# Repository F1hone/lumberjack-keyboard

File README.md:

# Lumberjack - Through-hole ortholinear 60% keyboard PCB

Lumberjack is a split 5x12 ortholinear keyboard PCB using through-hole components only.

The goal of this project is to build an all through-hole component ortholinear PCB that fits in a standard 60% tray mount case.

Inspired by the [Plaid keyboard](https://github.com/hsgw/plaid).

* Designed to be easy to build with minimal soldering experience.
* All through-hole components, no SMD soldering required.
* Get that visible component aesthetic in a standard 60% tray-mount case.
* Supports both USB Mini and USB-C.
* Plateless or with FR4 switch plates.

# Ordering parts

See the [Bill of materials](BOM.md) for a detailed list of the required parts.

PCBs can be manufactuered by a variety of online PCB fabricators. You can use [PCBShopper](https://pcbshopper.com/) to search for the best price.

The [zip file in the gerber directory](https://github.com/peej/lumberjack-keyboard/blob/master/gerber/lumberjack.zip) contains the gerber files your fabricator will need to make the PCB.

When uploading the gerber zip files, use the default PCB settings.

Note that when uploading to JLCPCB, the upload tool may not detect the dimensions of the PCB from the gerber files and may not generate a preview image. This appears to be an issue with JLCPCB and you can manually enter the PCB size as 94.6x285mm.

If you want to use a plate, there are gerbers for an FR4 plate. You will need two plates, one for each half of the keyboard.

# Construction

Solder all the components onto the top side of the PCB except the USB connector which should be on the back of the board. Leave the larger components until last so that the board will lie flat upsidedown while you solder the resistors and capacitors.

Take care to put the correct value resistors and capacitors in the correct places, the values are written on the silkmask along with the component reference. If you are unsure about the value of a resistor, check it with a multimeter.

Ensure that polarised components (diodes, LEDs, electrolytic capacitor (C3), IC socket) are in the correct orientation. The square pad is for the negative side of the component; for a diode this means the side with the black stripe; for LEDs and C3 the short leg is the cathode and goes in the square pad.

See [the build guide](guide.md) for more information.

## Need help?

Have questions or need help, reach out via [our Discord server](https://discord.gg/cQ9EXqQmpE) where you will find many helpful Lumberjack owners.

# Firmware

Firmware is available in the QMK repository under the name `peej/lumberjack`.

Follow the [QMK firmware instructions](https://docs.qmk.fm/#/flashing) to build and flash the firmware.

To put the board into bootloader mode so it is ready to recieve firmware, press and hold the BOOT button (SW2) while pressing and releasing the RESET button (SW1). The board will now be detected as an USBasp device and can have the firmware flashed via the USB port.

Pressing the RESET button (SW1) on its own will restart the microprocessor. Once flashed with firmware it is neccessary to reset the keyboard so as to return control to the new firmware.

Note that due to the BOOT button (SW2) sharing a pin with column 3, when pressed the keys in that column will also activate. This is expected behavour but can be a little annoying or confusing if you are not expecting it.

## VIA

There is a VIA compatible firmware available in QMK. With this firmware flashed, the board will be automatically recognised by VIA when you plug it in.

## Bootloader

If you have a "raw" chip without a bootloader, you will need to compile and flash the bootloader onto the chip via another device. [See the build guide for more information](guide.md#bootloader).

## Matrix information

If you are building your own firmware, the following matrix information will be useful to you:

| Configuration   | Value                                  |
|-----------------|----------------------------------------|
| MATRIX_ROWS     | 6                                      |
| MATRIX_COLS     | 10                                     |
| MATRIX_ROW_PINS | C0, B5, B4, B3, B2, B1                 |
| MATRIX_COL_PINS | B0, D7, D6, D5, D4, D1, D0, C1, C2, C3 |
| DIODE_DIRECTION | COL2ROW                                |

Due to the limited pin number of the ATMEGA328P, the PCB uses a 6 by 10 matrix (16 pins) instead of a 5 by 12 matrix (17 pins), this makes organising the matrix in your firmware slightly more complicated. The image below shows pins for each key.

# Component cover

Cut a piece of 2mm thick acrylic to size (95x57mm) and drill 4 m2 holes in the corners for the standoffs. Use the PCB or cover.dxf as a guide for the hole positions, you can also use cover.dxf for laser cutting the correct size acrylic.

Affix the 4 standoffs to the PCB with screws from underneath the PCB. Use the remaining 4 screws to attach the acrylic to the top of the standoffs.

# Electronic component cradles

Want to give your components the comfort they need, right?

These 3d printable cradles for your electornic components provided by 
SuPaSeM#3659 (discord) will hold things in place, keep them neat and tidy, and cradle your components like a baby.

# Revisions

## Rev 1.1

* Fix cosmetic errors in silkscreen
* Increase resistor footprint size
* Fix R1 resistor connection to D-

## Rev 1.2

* Add JST socket footprint for USB daughterboard
* Rotate central mount hole 90 degrees

## Rev 1.3

* Add hybrid USB port footprint for mini and type C
* Fix numbering of zener diode footprints
* Flip MX7 to be south facing

## Rev 1.4

* Use USB footprint with better positioning
* Move 5.1k resistors to better location
* Change MX8 to allow both north and south facing switch
## Rev 1.5

* Change board outline to include cutouts for Bakeneko 60
* Re-route traces away from edges of the board
* Change MX footprints to MX/Alps/Choc combined footprint
* Add through-hole JST connector footprint
* Add silkscreen art to underside

## Rev 1.6

* Add mounting holes for standoffs so PCB can be used without a case

## Rev 1.7

* Change board outline to include cutouts for Cannon Keys Bakeneko and Singa Unikorn

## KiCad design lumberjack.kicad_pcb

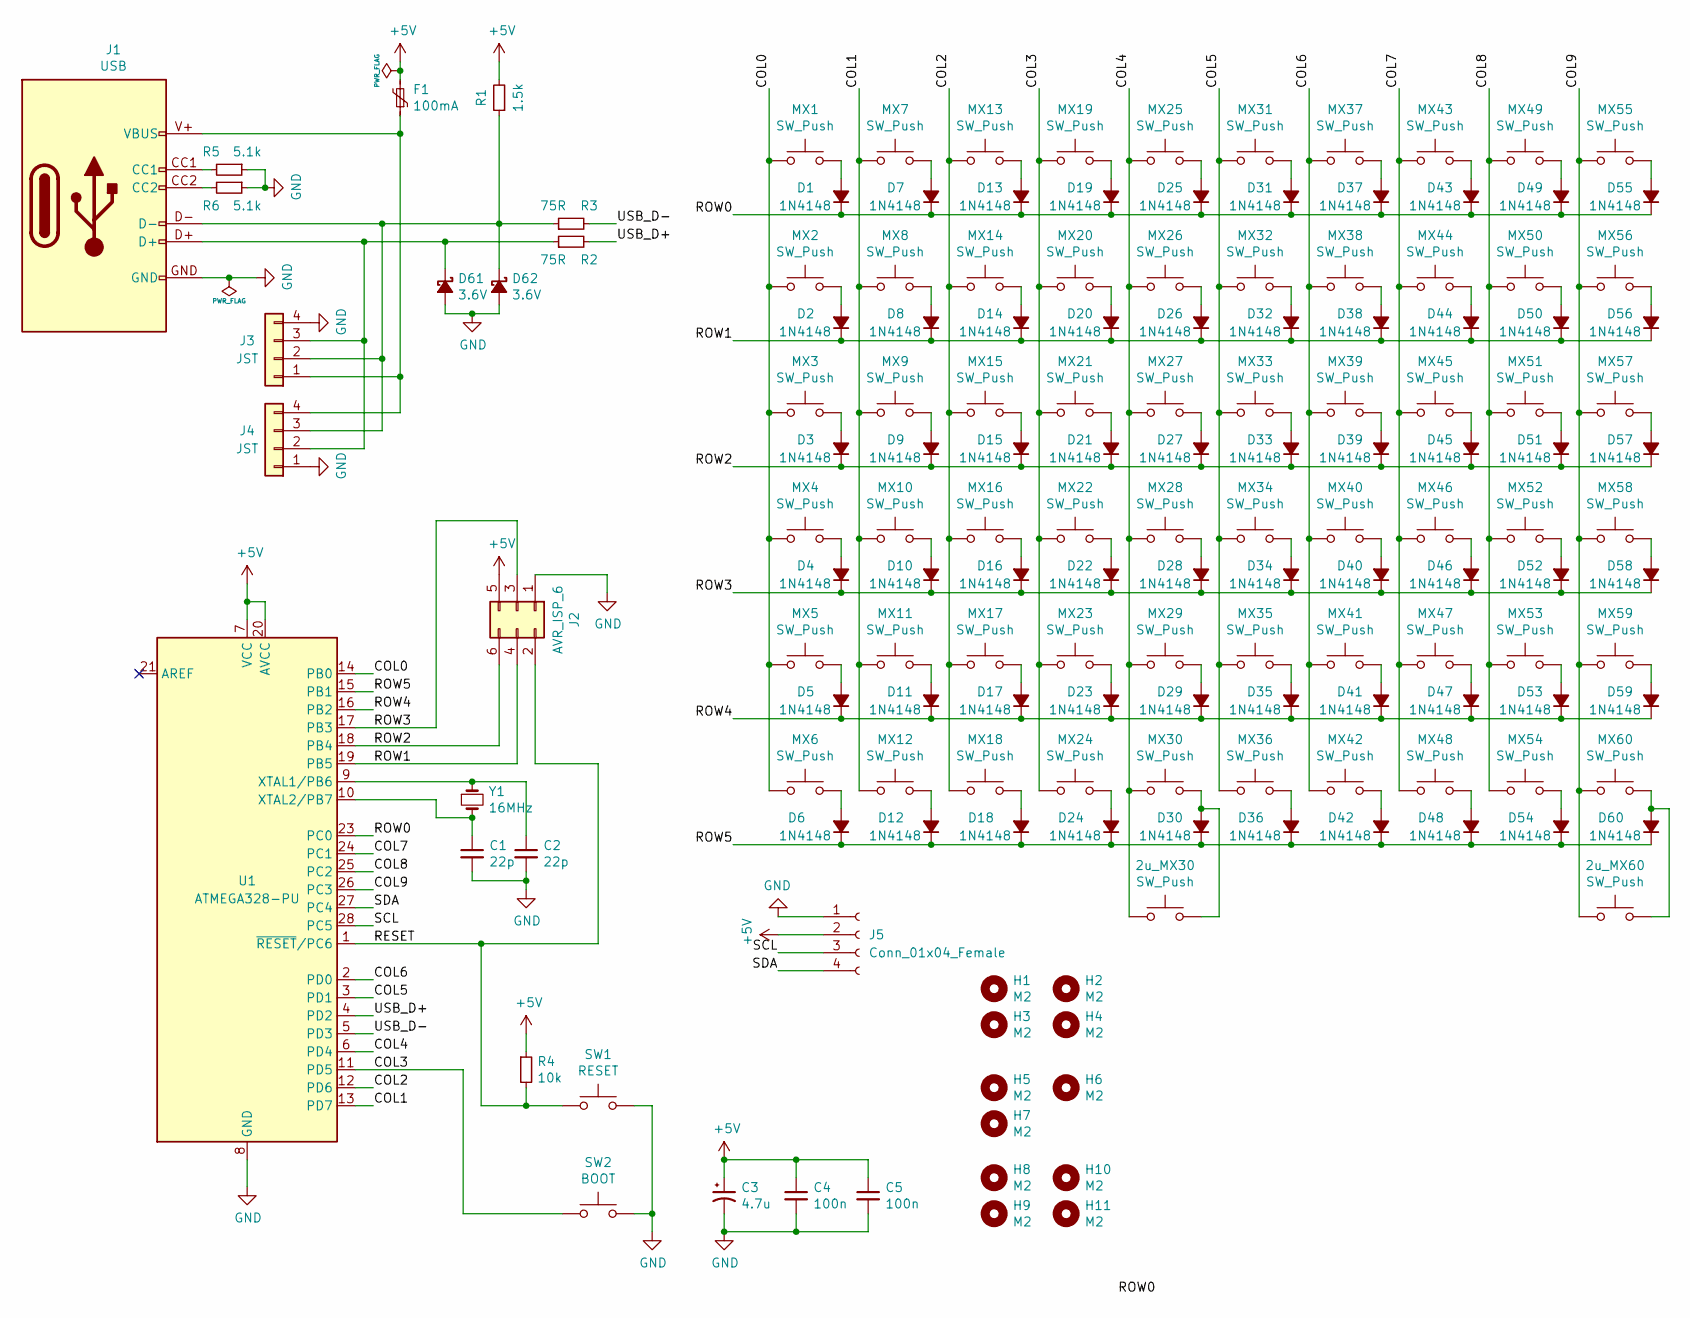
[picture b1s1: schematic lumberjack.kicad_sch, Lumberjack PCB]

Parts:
2u_MX30, 2u_MX60: SW_Push; MX_PCB_200B
C1, C2: 22p; C_Disc_D3.0mm_W1.6mm_P2.50mm
C3: 4.7u; CP_Radial_D4.0mm_P1.50mm
C4, C5: 100n; C_Disc_D4.3mm_W1.9mm_P5.00mm
D1, D2, D3, D4, D5, D6, D7, D8, D9, D10, D11, D12, D13, D14, D15, D16, D17, D18, D19, D20, D21, D22, D23, D24, D25, D26, D27, D28, D29, D30, D31, D32, D33, D34, D35, D36, D37, D38, D39, D40, D41, D42, D43, D44, D45, D46, D47, D48, D49, D50, D51, D52, D53, D54, D55, D56, D57, D58, D59, D60: 1N4148; D_DO-35_SOD27_P7.62mm_Horizontal
D61, D62: 3.6V; D_DO-35_SOD27_P7.62mm_Horizontal
F1: 100mA; Fuse_Bourns_MF-RHT100
H1, H2, H3, H4, H8, H9, H10, H11: M2; MountingHole_M2
H5, H6, H7: M2; MountingSlot_M2
J1: USB; USB_Hybrid
J2: AVR_ISP_6; PinHeader_2x03_P2.54mm_Vertical
J3: JST; JST_SH_SM04B-SRSS-TB_1x04-1MP_P1.00mm_Horizontal
J4: JST; S4B-ZRLFSN
J5: Conn_01x04_Female; PinHeader_1x04_P2.54mm_Vertical
MX1, MX2, MX3, MX4, MX5, MX6, MX7, MX9, MX10, MX11, MX12, MX13, MX14, MX15, MX16, MX17, MX18, MX19, MX20, MX21, MX22, MX23, MX24, MX25, MX26, MX27, MX28, MX29, MX30, MX31, MX32, MX33, MX34, MX35, MX36, MX37, MX38, MX39, MX40, MX41, MX42, MX43, MX44, MX45, MX46, MX47, MX48, MX49, MX50, MX51, MX52, MX53, MX54, MX55, MX56, MX57, MX58, MX59, MX60: SW_Push; MX_Alps_Choc
MX8: SW_Push; MX_Alps_Choc_NTHSTH
R1: 1.5k; R_Axial_DIN0204_L3.6mm_D1.6mm_P7.62mm_Horizontal
R2, R3: 75R; R_Axial_DIN0204_L3.6mm_D1.6mm_P7.62mm_Horizontal
R4: 10k; R_Axial_DIN0204_L3.6mm_D1.6mm_P7.62mm_Horizontal
R5, R6: 5.1k; R_Axial_DIN0204_L3.6mm_D1.6mm_P7.62mm_Horizontal
SW1: RESET; SW_PUSH_6mm
SW2: BOOT; SW_PUSH_6mm
U1: ATMEGA328-PU; DIP-28_W7.62mm
Y1: 16MHz; Crystal_HC49-4H_Vertical

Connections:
+5V: C3.1, C4.1, C5.1, F1.2, J2.5, J5.2, R1.2, R4.1, U1.7 (VCC), U1.20 (AVCC)
/COL0: MX1.2, MX2.2, MX3.2, MX4.2, MX5.2, MX6.2, U1.14 (PB0)
/COL1: MX7.2, MX8.2, MX9.2, MX10.2, MX11.2, MX12.2, U1.13 (PD7)
/COL2: MX13.2, MX14.2, MX15.2, MX16.2, MX17.2, MX18.2, U1.12 (PD6)
/COL3: MX19.2, MX20.2, MX21.2, MX22.2, MX23.2, MX24.2, SW2.1, U1.11 (PD5)
/COL4: 2u_MX30.2, MX25.2, MX26.2, MX27.2, MX28.2, MX29.2, MX30.2, U1.6 (PD4)
/COL5: MX31.2, MX32.2, MX33.2, MX34.2, MX35.2, MX36.2, U1.3 (PD1)
/COL6: MX37.2, MX38.2, MX39.2, MX40.2, MX41.2, MX42.2, U1.2 (PD0)
/COL7: MX43.2, MX44.2, MX45.2, MX46.2, MX47.2, MX48.2, U1.24 (PC1)
/COL8: MX49.2, MX50.2, MX51.2, MX52.2, MX53.2, MX54.2, U1.25 (PC2)
/COL9: 2u_MX60.2, MX55.2, MX56.2, MX57.2, MX58.2, MX59.2, MX60.2, U1.26 (PC3)
/RESET: J2.2, R4.2, SW1.1, U1.1 (~RESET/PC6)
/ROW0: D1.1 (K), D7.1 (K), D13.1 (K), D19.1 (K), D25.1 (K), D31.1 (K), D37.1 (K), D43.1 (K), D49.1 (K), D55.1 (K), U1.23 (PC0)
/ROW1: D2.1 (K), D8.1 (K), D14.1 (K), D20.1 (K), D26.1 (K), D32.1 (K), D38.1 (K), D44.1 (K), D50.1 (K), D56.1 (K), J2.4, U1.19 (PB5)
/ROW2: D3.1 (K), D9.1 (K), D15.1 (K), D21.1 (K), D27.1 (K), D33.1 (K), D39.1 (K), D45.1 (K), D51.1 (K), D57.1 (K), J2.6, U1.18 (PB4)
/ROW3: D4.1 (K), D10.1 (K), D16.1 (K), D22.1 (K), D28.1 (K), D34.1 (K), D40.1 (K), D46.1 (K), D52.1 (K), D58.1 (K), J2.3, U1.17 (PB3)
/ROW4: D5.1 (K), D11.1 (K), D17.1 (K), D23.1 (K), D29.1 (K), D35.1 (K), D41.1 (K), D47.1 (K), D53.1 (K), D59.1 (K), U1.16 (PB2)
/ROW5: D6.1 (K), D12.1 (K), D18.1 (K), D24.1 (K), D30.1 (K), D36.1 (K), D42.1 (K), D48.1 (K), D54.1 (K), D60.1 (K), U1.15 (PB1)
/SCL: J5.3, U1.28 (PC5)
/SDA: J5.4, U1.27 (PC4)
/USB_D+: R2.2, U1.4 (PD2)
/USB_D-: R3.2, U1.5 (PD3)
GND: C1.2, C2.2, C3.2, C4.2, C5.2, D61.2 (A), D62.2 (A), J1.GND, J2.1, J3.4, J4.1, J5.1, R5.1, R6.1, SW1.2, SW2.2, U1.8 (GND), U1.22 (GND); also elsewhere on the board
unnamed: 2u_MX30.1, D30.2 (A), MX30.1
unnamed: 2u_MX60.1, D60.2 (A), MX60.1
unnamed: C1.1, U1.10 (XTAL2/PB7), Y1.2
unnamed: C2.1, U1.9 (XTAL1/PB6), Y1.1
unnamed: D1.2 (A), MX1.1
unnamed: D2.2 (A), MX2.1
unnamed: D3.2 (A), MX3.1
unnamed: D4.2 (A), MX4.1
unnamed: D5.2 (A), MX5.1
unnamed: D6.2 (A), MX6.1
unnamed: D7.2 (A), MX7.1
unnamed: D8.2 (A), MX8.1
unnamed: D9.2 (A), MX9.1
unnamed: D10.2 (A), MX10.1
unnamed: D11.2 (A), MX11.1
unnamed: D12.2 (A), MX12.1
unnamed: D13.2 (A), MX13.1
unnamed: D14.2 (A), MX14.1
unnamed: D15.2 (A), MX15.1
unnamed: D16.2 (A), MX16.1
unnamed: D17.2 (A), MX17.1
unnamed: D18.2 (A), MX18.1
unnamed: D19.2 (A), MX19.1
unnamed: D20.2 (A), MX20.1
unnamed: D21.2 (A), MX21.1
unnamed: D22.2 (A), MX22.1
unnamed: D23.2 (A), MX23.1
unnamed: D24.2 (A), MX24.1
unnamed: D25.2 (A), MX25.1
unnamed: D26.2 (A), MX26.1
unnamed: D27.2 (A), MX27.1
unnamed: D28.2 (A), MX28.1
unnamed: D29.2 (A), MX29.1
unnamed: D31.2 (A), MX31.1
unnamed: D32.2 (A), MX32.1
unnamed: D33.2 (A), MX33.1
unnamed: D34.2 (A), MX34.1
unnamed: D35.2 (A), MX35.1
unnamed: D36.2 (A), MX36.1
unnamed: D37.2 (A), MX37.1
unnamed: D38.2 (A), MX38.1
unnamed: D39.2 (A), MX39.1
unnamed: D40.2 (A), MX40.1
unnamed: D41.2 (A), MX41.1
unnamed: D42.2 (A), MX42.1
unnamed: D43.2 (A), MX43.1
unnamed: D44.2 (A), MX44.1
unnamed: D45.2 (A), MX45.1
unnamed: D46.2 (A), MX46.1
unnamed: D47.2 (A), MX47.1
unnamed: D48.2 (A), MX48.1
unnamed: D49.2 (A), MX49.1
unnamed: D50.2 (A), MX50.1
unnamed: D51.2 (A), MX51.1
unnamed: D52.2 (A), MX52.1
unnamed: D53.2 (A), MX53.1
unnamed: D54.2 (A), MX54.1
unnamed: D55.2 (A), MX55.1
unnamed: D56.2 (A), MX56.1
unnamed: D57.2 (A), MX57.1
unnamed: D58.2 (A), MX58.1
unnamed: D59.2 (A), MX59.1
unnamed: D61.1 (K), J1.D+, J3.3, J4.2, R2.1
unnamed: D62.1 (K), J1.D-, J3.2, J4.3, R1.1, R3.1
unnamed: F1.1, J1.V+ (VBUS), J3.1, J4.4
unnamed: J1.CC1, R5.2
unnamed: J1.CC2, R6.2

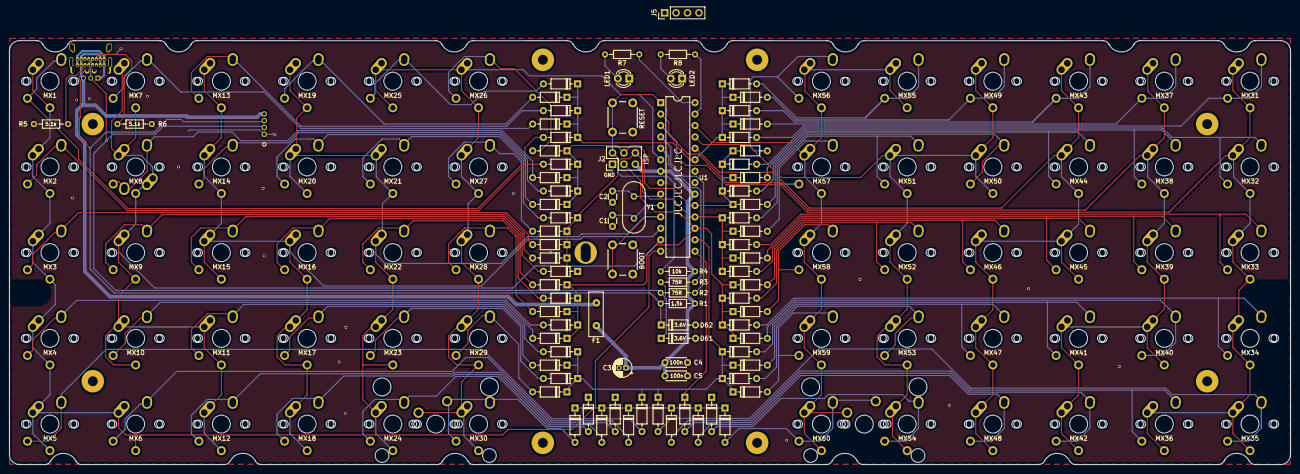
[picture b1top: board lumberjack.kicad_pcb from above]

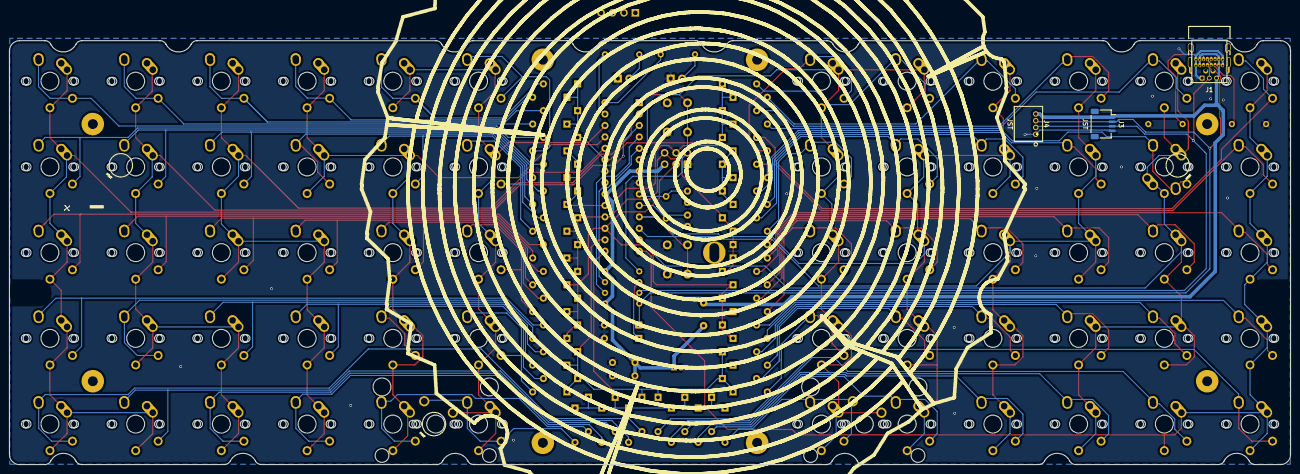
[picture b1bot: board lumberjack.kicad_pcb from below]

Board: 2 copper layers, 284.7 x 94.2 mm, 160 parts (3 on the bottom side), 92 nets.

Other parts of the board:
LED1: RED; LED_D3.0mm
LED2: GREEN; LED_D3.0mm
R7, R8: 1.5k; R_Axial_DIN0204_L3.6mm_D1.6mm_P7.62mm_Horizontal

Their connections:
GND: LED1.1 (K), LED2.1 (K); also elsewhere on the board
unnamed: LED1.2 (A), R7.2
unnamed: LED2.2 (A), R8.2

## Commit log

2023-02-08 修改丝印，增加屏幕插座
2023-02-12 更改了led，增加oled屏幕

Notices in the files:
parts and their libraries:
Copyright 2021 Accelerated Designs. All rights reserved.
